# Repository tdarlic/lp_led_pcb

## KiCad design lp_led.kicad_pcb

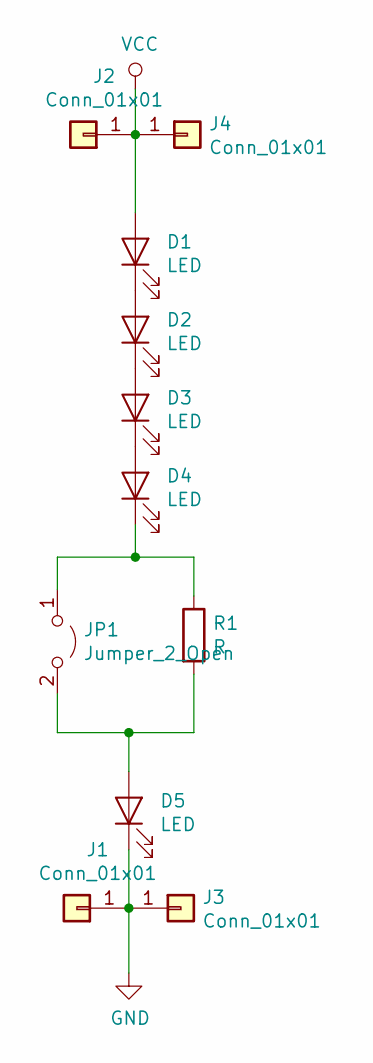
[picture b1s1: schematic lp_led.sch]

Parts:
D1, D2, D3, D4, D5: LED; OSRAM_LA_T68B
J1, J2, J3, J4: Conn_01x01; EDGE_PAD
JP1: Jumper_2_Open; SolderJumper-2_P1.3mm_Open_TrianglePad1.0x1.5mm
R1: R; R_0805_2012Metric_Pad1.15x1.40mm_HandSolder

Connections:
GND: D5.1 (K), J1.1, J3.1
unnamed: D1.1 (K), D2.2 (A)
unnamed: D2.1 (K), D3.2 (A)
unnamed: D3.1 (K), D4.2 (A)
unnamed: D4.1 (K), JP1.1 (A), R1.1
unnamed: D5.2 (A), JP1.2 (B), R1.2
VCC: D1.2 (A), J2.1, J4.1

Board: 2 copper layers, 11 parts (0 on the bottom side), 7 nets, no tracks yet.

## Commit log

2018-12-24 Adding gitignore
